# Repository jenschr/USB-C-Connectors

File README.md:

# USB-C-Connectors
Various cheap USB-C connectors from LCSC for KiCad. Brief [rundown of the USB standards here](https://flashgamer.com/blog/comments/usb-type-c-and-usb-2.0-3.0-3.1-3.2) and details on [how to use these boards here.](https://flashgamer.com/blog/comments/implementing-usb-type-c-and-usb-3-1)

## Why?
I want to move over to use USB C connectors in my designs and I want more options than just using the few predefined in Kicad.

Price is also relevant. Amphenol and Molex are fantastic connectors, but of the three footprints that come with Kicad 5, Amphenol 12401548E4#2A and Molex 105444 are no longer being made. The third Type C connector is 12401610E4#2A. It's 2 USD for one and 1.35 USD for 100 pcs.

If you just want a USB C connector for applying power, you can get this from a good Korean factory for 0.21 USD at LCSC. This is if you only buy a single connector. Buy a hundred and save 7 of those cents - down to 0.14 USD. Want USB 2.0? The price starts at 0.38 USD for just one, but gets down to 0.24 USD if you buy a hundred. A fully featured USB 3.1 connector is 0.81 USD, so still below half the price.

## A quick note on durability
I've now used the USB connectors from Korean Hroparts Elec in more than 5k boards and they hold up well - even for things like devboards that are plugged in/out daily.

TYPE-C-31-M-12 used to be my goto part for USB2.0, but I've found that the official footprint for these can cause problems with many board houses. The pins on the part only stick out 0.9mm, so if the board shop don't fully fill the 1.6mm hole - you'll have cases where the part rips off. I've now started using TYPE-C-31-M-14 as the new goto. This one is seated inside the board and I've never had a soldering problem with it. I'm not 100% sure why it's so much more successful, but I guess it's something about wicking during selective/wave soldering. When using TYPE-C-31-M-14, you should be aware of it's rather low ampacity rating (1A) compared to many other Type C connectors (typically 5A).

## Versions. Errata

### 2022.03.09
Four new footprints added:
- TYPE-C-31-M-14 (USB3.0 Type C, edge/flush mounted) from Korean Hroparts Elec @ LCSC
- U-A-39DS-Y-1 (USB3.0 Type A) from Korean Hroparts Elec @ LCSC
- U-B-M9DD-W-1 (USB3.0 Type B) from Korean Hroparts Elec @ LCSC
- U-F-10SW-Y-1 (USB3.0 Micro B) from Korean Hroparts Elec @ LCSC

Minor tweak to power pads on two footprints. All footprints have been tested and used extensively in several boards now.

### 2020.05.20
Got the second batch of boards. All 3 footprints are now golden!

### 2020.05.04
Got the first batch of boards today. The Power board was good, the USB 2.0 board required that you cut off two tiny alignment pins (plastic) that I forgot to include in the footprint, but works otherwise great. The USB 3.1 board has an error that cannot be fixed (pins in wrong place), so I've made a new version of that and sent it to PCBWay. All footprints in the repo should now be good, but it'll take about a week until I can confirm that.

## Kicad files:
I've made breakout boards to test my footprints. The files are available in the Kicad repo and these are now tested and confirmed. I placed orders for the first boards on April 25th 2020.
 
### Footprints
Library with footprints for low priced Type C & USB3 connectors and alternates.

### USB-C-Power-tester
Simple Breakout board allowing you to play with setting CC1 & CC2 using easy to solder 0805 resistors. Read up on the [USB-IF spec and what resistors to use here](http://ww1.microchip.com/downloads/en/appnotes/00001953a.pdf). These connectors offer no data, but can let you pull or deliver up to 3A/5V power from capable devices.

Compatible part numbers:
- TYPE-C-31-M-17 from Korean Hroparts Elec @ LCSC
- USB4125-GF-A from GCT @ Digikey

### USB-C-USB-2.0
Simple Breakout board exposing all you need for USB 2.0 using a Type C connector. Also has room for resistors for CC1 & CC2 as the power breakout above.

Compatible part numbers:
- TYPE-C-31-M-12 from Korean Hroparts Elec @ LCSC
- USB4105-GF-A from GCT @ Digikey
- CU3216SASDLR010-NH from Civlux @ Digikey

### USB-C-USB-3.2
Breakout board for a fully featured USB 3.2 connector that can be used with a low priced IC for cable detection, orientation, data switching and power settings. 

When using this board, don't forget that to get higher speeds to work, you'll need sub-millimeter precision on your cable lengths. All RX/TX pairs should be the exact same length, just as they are one the PCB. Don't expect SuperSpeed to work if you're using a breadboard for prototyping.

Compatible part numbers:
- U262-241N-4BV60 from XKB Connectivity @ LCSC
- TYPE-C-31-M-04 from Korean Hroparts Elec @ LCSC
- 10137062-00021LF from Amphenol ICC @ Digikey

## Stuff to remember
- When placing resistors for CC1 & CC2, keep in mind that DFP (PC/Hub or similar) is the host offering power to a UFP (Device). This way, the Device can know how much power the Host can supply and act based on that.
- With a Type C cable, you do not know the orientation. If you want to use USB 3.X features, you'll have to detect the orientation and select which of the RX/TX pairs to use, in addition to applying the correct current according to CC1 & CC2. This is usually done using custom silicone such as the TUSB320.

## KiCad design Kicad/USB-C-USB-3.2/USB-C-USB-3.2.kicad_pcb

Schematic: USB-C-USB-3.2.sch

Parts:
H1: MountingHole; MountingHole_3.2mm_M3_Pad_Via
H3: MountingHole; MountingHole_3.2mm_M3_Pad
J1: Screw_Terminal_01x16; PinHeader_1x16_P2.54mm_Vertical
L1: Logo_Open_Hardware_Small; OSHW-Logo_5.7x6mm_Copper
L2: Logo_Open_Hardware_Small; Bitraf_logo_3.0_x_7.5_mm
P1: USB_C_Plug; USB_C_Receptacle_Amphenol_12401548E4-2A
R1: 1M; R_0805_2012Metric_Pad1.15x1.40mm_HandSolder

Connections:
/CC1: J1.3, P1.A5
/CC2: J1.14, P1.B5
/D+: J1.9, P1.A6
/D-: J1.8, P1.A7
/RX1+: J1.12, P1.B11
/RX1-: J1.13, P1.B10
/RX2+: J1.6, P1.A11
/RX2-: J1.7, P1.A10
/SBU1: J1.2, P1.A8
/SBU2: J1.15, P1.B8
/TX1+: J1.11, P1.A2
/TX1-: J1.10, P1.A3
/TX2+: J1.5, P1.B2
/TX2-: J1.4, P1.B3
GND: J1.16, P1.A1, P1.A12, P1.B1, P1.B12, R1.1
unnamed: P1.S1, R1.2
VBUS: J1.1, P1.A4, P1.A9, P1.B4, P1.B9

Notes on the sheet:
See USB IF spec, Microchip Appnote AN1953, chapter 3.0 to set resistors

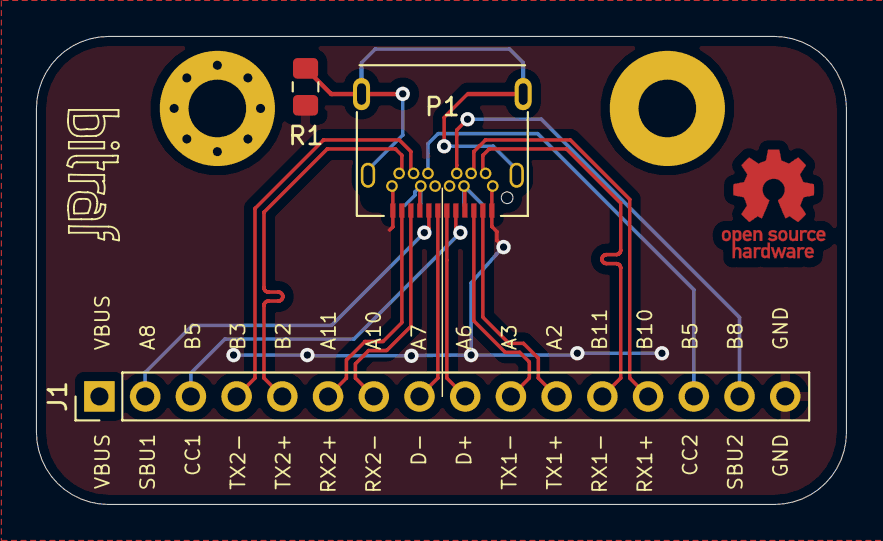
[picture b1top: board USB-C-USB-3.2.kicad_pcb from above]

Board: 2 copper layers, 45.0 x 26.0 mm, 7 parts (0 on the bottom side), 17 nets.

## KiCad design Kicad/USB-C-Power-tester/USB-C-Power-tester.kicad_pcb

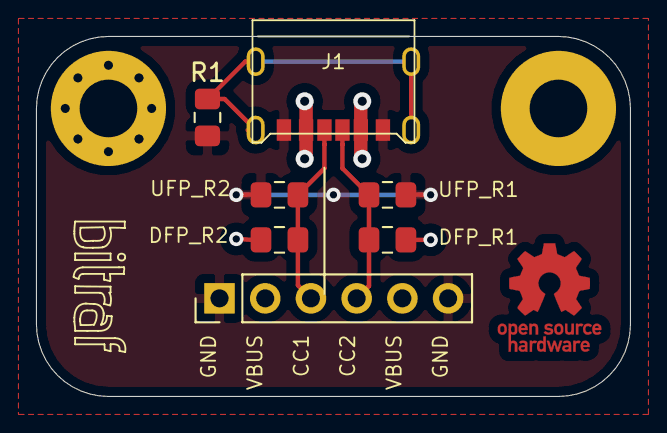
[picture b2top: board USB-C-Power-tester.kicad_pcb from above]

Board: 2 copper layers, 33.0 x 20.0 mm, 11 parts (0 on the bottom side), 5 nets.

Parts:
DFP_R1, DFP_R2: DFP; R_0805_2012Metric_Pad1.15x1.40mm_HandSolder
H1: MountingHole; MountingHole_3.2mm_M3_Pad_Via
H3: MountingHole; MountingHole_3.2mm_M3_Pad
J1: USB_C_Receptacle_USB2.0; TYPE-C-31-M-17
L1: Logo_Open_Hardware_Small; OSHW-Logo_5.7x6mm_Copper
L2: Logo_Open_Hardware_Small; Bitraf_logo_3.0_x_7.5_mm
PIN1: Screw_Terminal_01x06; PinHeader_1x06_P2.54mm_Vertical
R1: 1M; R_0805_2012Metric_Pad1.15x1.40mm_HandSolder
UFP_R1, UFP_R2: UFP; R_0805_2012Metric_Pad1.15x1.40mm_HandSolder

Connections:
GND: J1.A12, J1.B12, PIN1.1, PIN1.6, R1.1, UFP_R1.2, UFP_R2.2
unnamed: DFP_R1.1, J1.A5, PIN1.4, UFP_R1.1
unnamed: DFP_R2.1, J1.B5, PIN1.3, UFP_R2.1
unnamed: J1.S1, R1.2
VBUS: DFP_R1.2, DFP_R2.2, J1.A9, J1.B9, PIN1.2, PIN1.5

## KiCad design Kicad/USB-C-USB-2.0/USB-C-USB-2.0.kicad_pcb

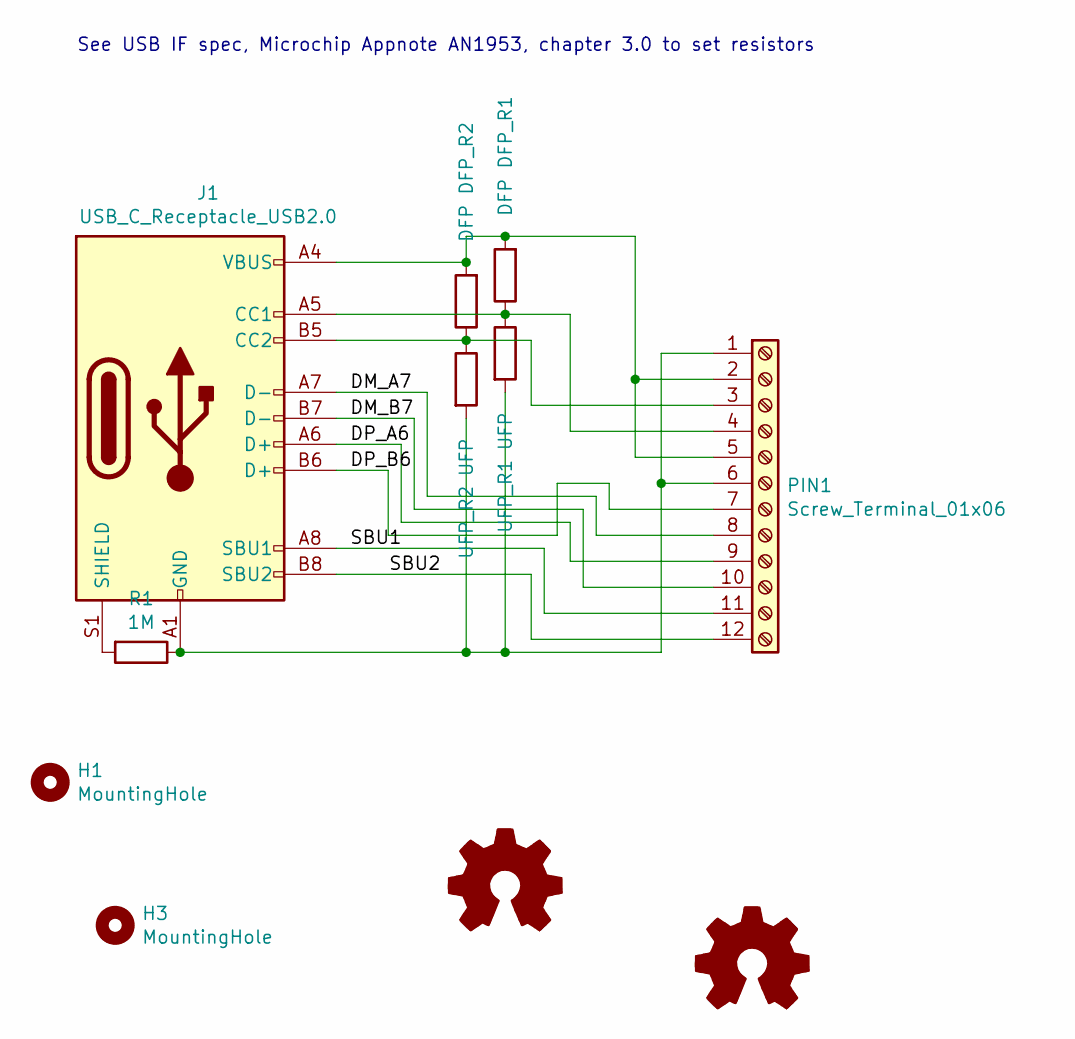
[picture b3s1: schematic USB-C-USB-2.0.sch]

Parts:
DFP_R1, DFP_R2: DFP; R_0805_2012Metric_Pad1.15x1.40mm_HandSolder
H1: MountingHole; MountingHole_3.2mm_M3_Pad_Via
H3: MountingHole; MountingHole_3.2mm_M3_Pad
J1: USB_C_Receptacle_USB2.0; TYPE-C-31-M-12; MPN TYPE-C-31-M-17
L1: Logo_Open_Hardware_Small; OSHW-Logo_5.7x6mm_SilkScreen
L2: Logo_Open_Hardware_Small; Bitraf_logo_3.0_x_7.5_mm
PIN1: Screw_Terminal_01x06; PinHeader_1x12_P2.54mm_Vertical
R1: 1M; R_0805_2012Metric_Pad1.15x1.40mm_HandSolder
UFP_R1, UFP_R2: UFP; R_0805_2012Metric_Pad1.15x1.40mm_HandSolder

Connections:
/DM_A7: J1.A7 (D-), PIN1.8
/DM_B7: J1.B7 (D-), PIN1.10
/DP_A6: J1.A6 (D+), PIN1.9
/DP_B6: J1.B6 (D+), PIN1.7
/SBU1: J1.A8 (SBU1), PIN1.11
/SBU2: J1.B8 (SBU2), PIN1.12
GND: J1.A1 (GND), J1.A12 (GND), J1.B1 (GND), J1.B12 (GND), PIN1.1, PIN1.6, R1.1, UFP_R1.2, UFP_R2.2
unnamed: DFP_R1.1, J1.A5 (CC1), PIN1.4, UFP_R1.1
unnamed: DFP_R2.1, J1.B5 (CC2), PIN1.3, UFP_R2.1
unnamed: J1.S1 (SHIELD), R1.2
VBUS: DFP_R1.2, DFP_R2.2, J1.A4 (VBUS), J1.A9 (VBUS), J1.B4 (VBUS), J1.B9 (VBUS), PIN1.2, PIN1.5

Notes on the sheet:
See USB IF spec, Microchip Appnote AN1953, chapter 3.0 to set resistors

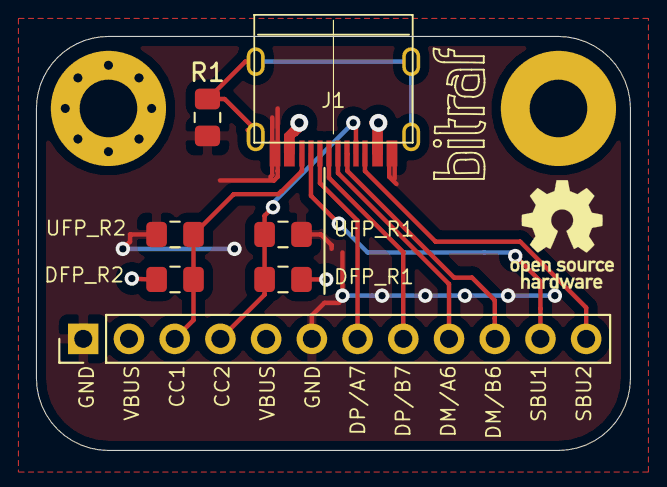
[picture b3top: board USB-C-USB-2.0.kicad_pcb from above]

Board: 2 copper layers, 33.0 x 23.0 mm, 11 parts (0 on the bottom side), 11 nets.

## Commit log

2020-04-24 First two boards & text
2020-04-24 typos, better wording
2020-04-26 USB 3.2 PCB
2020-04-26 links
2020-04-27 Updated files & some images used in the article
2020-04-27 More images
2020-05-04 Added the most important datasheet
2020-05-05 Files and footprint adjusted for error and omission
2020-05-20 Updated footprints confirmed good
2021-02-09 Added 3 alternate parts from Digikey with compatible footprints. Nice to have since the cheap parts from Korean Hroparts Elec sometimes are sold out
    I might add that the Korean Hroparts Elec parts don't really wear that well. I've used them on prototype cards that I plug/unplug on a daily basis and they become "loose" over time. Makes me think th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
2021-02-14 Added another compatible part
2022-03-09 Added gitignore, slight trimming of pwoer pins on two footprints, added Type A, Type B and Micro footprints as well, added TYPE-C-31-M-14 that is more flush with the PCB since it's cut into it
2022-03-09 updated docs
2025-08-13 Verified & tested tweaks to some connectors. Added DX07S016JA3R1500.
2026-01-16 Note om ampacity
